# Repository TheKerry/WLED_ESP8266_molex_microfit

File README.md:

# WLED_ESP8266_molex_microfit

D1 will be assembled thr wrong way. It has to be rotated by 180° once the PCB arrives.

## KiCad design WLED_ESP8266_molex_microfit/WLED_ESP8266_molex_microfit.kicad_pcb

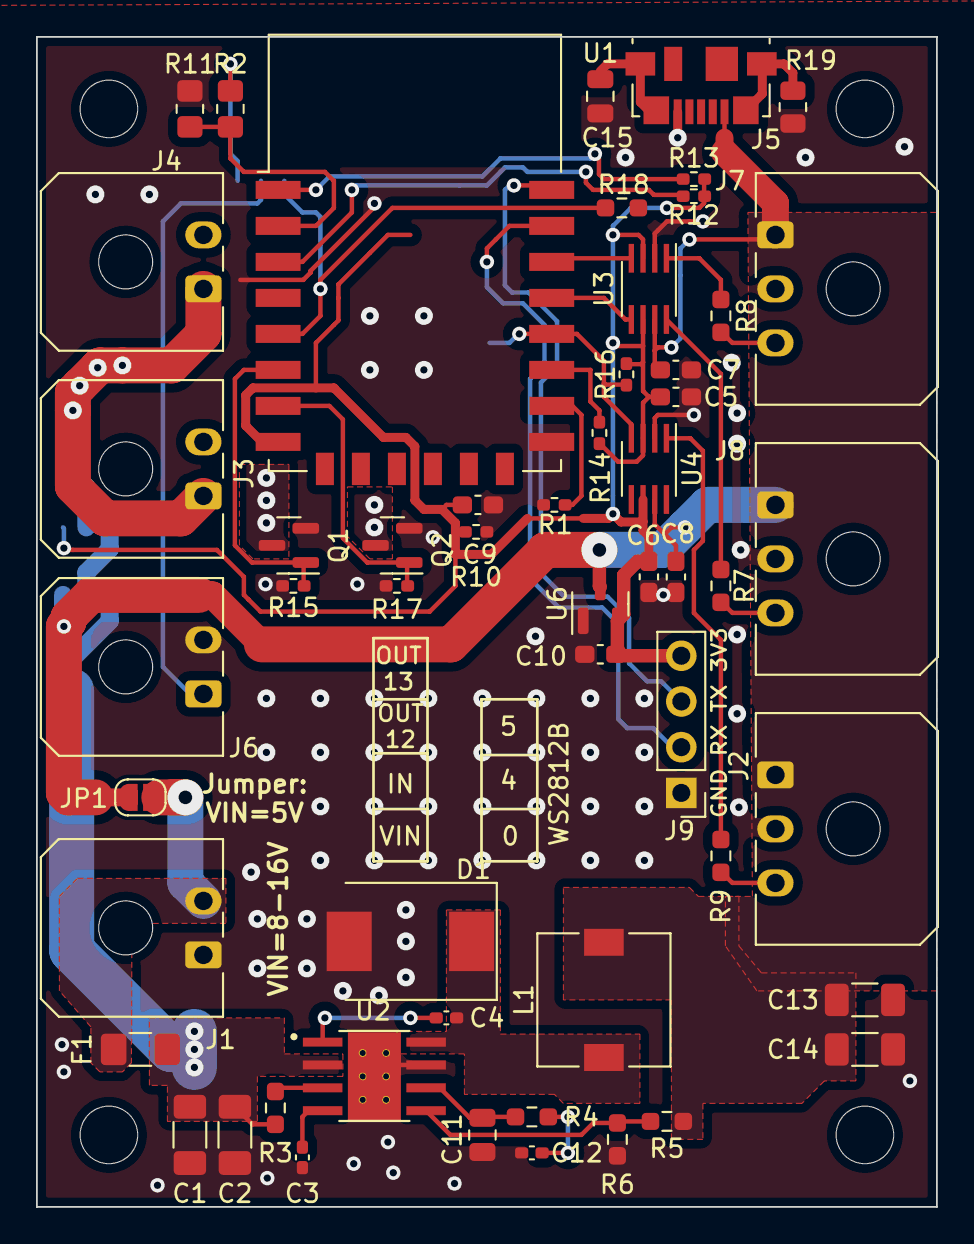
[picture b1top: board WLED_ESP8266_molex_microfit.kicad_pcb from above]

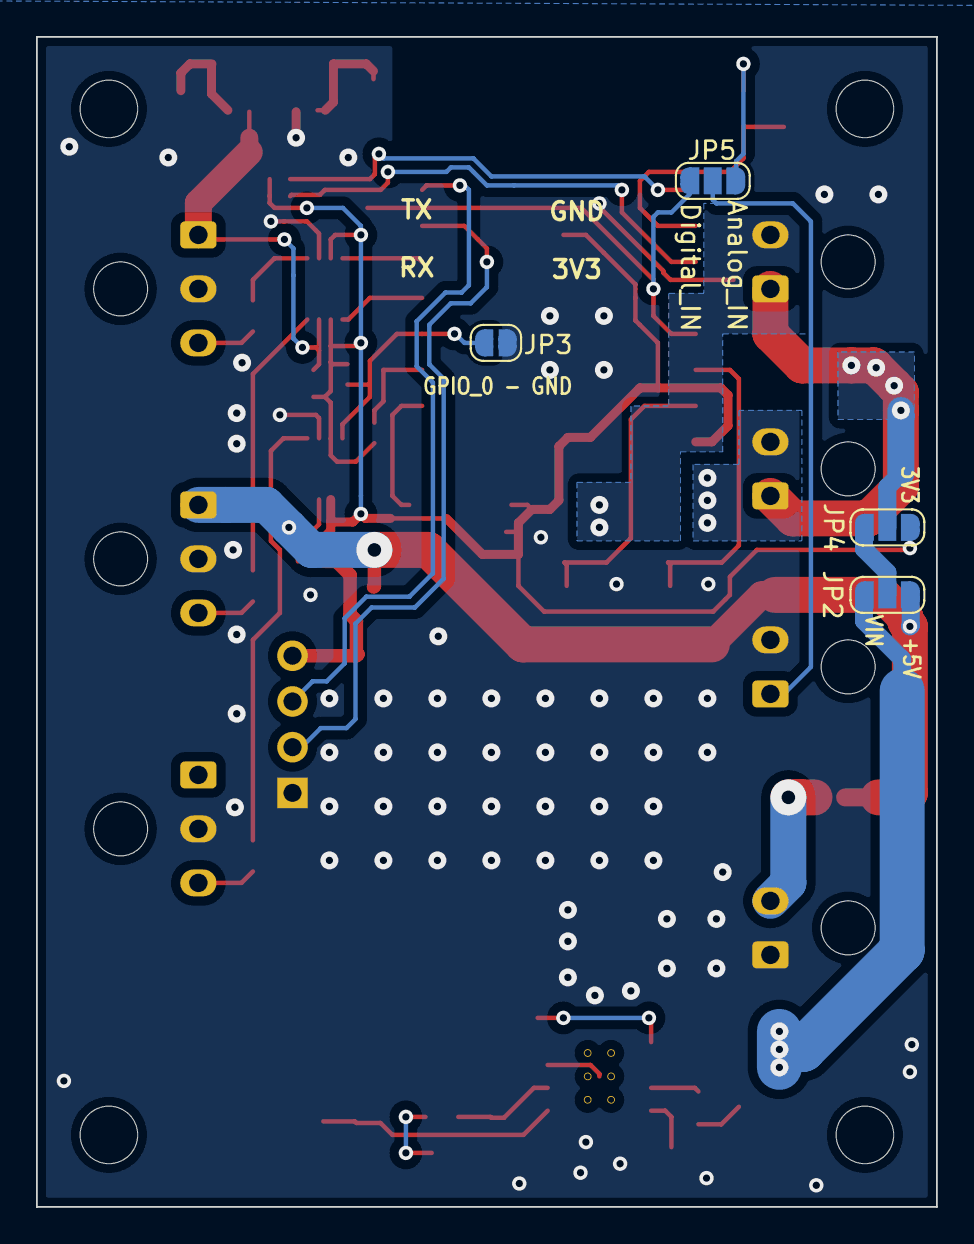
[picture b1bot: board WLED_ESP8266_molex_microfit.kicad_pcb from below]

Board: 2 copper layers, 50.0 x 65.0 mm, 62 parts (4 on the bottom side), 38 nets.

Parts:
C1, C2: 10uF; C_1206_3216Metric_Pad1.33x1.80mm_HandSolder
C3: 22uF; C_0402_1005Metric_Pad0.74x0.62mm_HandSolder
C4, C12: 100nF; C_0402_1005Metric_Pad0.74x0.62mm_HandSolder
C5, C6, C7, C8, C9, C10: 100nF; C_0603_1608Metric_Pad1.08x0.95mm_HandSolder
C11: 10pF; C_0805_2012Metric
C13, C14: 47uF; C_1206_3216Metric_Pad1.33x1.80mm_HandSolder
C15: 0.01uF; C_0805_2012Metric
D1: B340; D_SMC
F1: 5A; Fuse_1206_3216Metric_Pad1.42x1.75mm_HandSolder
H1, H2, H3, H4: MountingHole; MountingHole_3.2mm_M3_DIN965
J1, J3, J4, J6: Molex Micro-fit 2x1; Molex_Micro-Fit_3.0_43650-0200_1x02_P3.00mm_Horizontal
J2, J7, J8: Molex Micro-fit 3x1; Molex_Micro-Fit_3.0_43650-0300_1x03_P3.00mm_Horizontal
J5: USB_B_Micro; USB_Micro-B_Molex_47346-0001
J9: Conn_01x04_Male; PinHeader_1x04_P2.54mm_Vertical
JP1, JP3: SolderJumper_2_Open; SolderJumper-2_P1.3mm_Open_RoundedPad1.0x1.5mm
JP2, JP4, JP5: SolderJumper_3_Open; SolderJumper-3_P1.3mm_Open_RoundedPad1.0x1.5mm_NumberLabels
L1: 6.8uH; L_7.3x7.3_H3.5
Q1, Q2: AO3401A; SOT-23
R1, R10, R12, R13, R14, R15, R16, R17: 10k; R_0402_1005Metric_Pad0.72x0.64mm_HandSolder
R2: 68k; R_0805_2012Metric_Pad1.20x1.40mm_HandSolder
R3: 0; R_0603_1608Metric_Pad0.98x0.95mm_HandSolder
R4: 61.9k; R_0603_1608Metric_Pad0.98x0.95mm_HandSolder
R5: 10.2k; R_0603_1608Metric_Pad0.98x0.95mm_HandSolder
R6: 1.96k; R_0603_1608Metric_Pad0.98x0.95mm_HandSolder
R7, R8, R9: 300; R_0603_1608Metric_Pad0.98x0.95mm_HandSolder
R11: 4.7k; R_0805_2012Metric_Pad1.20x1.40mm_HandSolder
R18: 10k; R_0603_1608Metric_Pad0.98x0.95mm_HandSolder
R19: 1M; R_0805_2012Metric
U1: ESP-12F; ESP-12E
U2: TPS54331DDAR; CONV_TPS54331DDAR
U3, U4: TXS0102DCT; SSOP-8_2.95x2.8mm_P0.65mm
U6: ME6211A33M3G-N; SOT-23

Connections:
+3V3: C5.2, C6.2, C9.2, C10.2, J9.4, JP4.1 (A), R10.2, R12.2, R13.2, R14.2, R16.2, R18.2, U1.8 (VCC), U3.3 (VCCA), U3.6 (OE), U4.3 (VCCA), U4.6 (OE), U6.2 (VO)
+5V: C7.1, C8.1, C13.1, C14.1, J2.1, J5.1 (VBUS), J7.1, J8.1, JP1.2 (B), JP2.1 (A), L1.2, R5.2, U3.7 (VCCB), U4.7 (VCCB), U6.3 (VI)
/Q1_Drain: J3.2, Q1.3 (D)
/Q2_Drain: J4.2, Q2.3 (D)
/TPS_PH: C4.2, D1.1 (K), L1.1, U2.8 (PH)
ADC: JP5.1 (A), R2.1
EN: R12.1, U1.3 (EN)
GND: C1.2, C2.2, C3.1, C5.1, C6.1, C7.2, C8.2, C9.1, C10.1, C11.1, C12.1, C13.2, C14.2, C15.2, D1.2 (A), J1.1, J2.2, J5.5 (GND), J6.2, J7.2, J8.2, J9.1, JP3.2 (B), Q1.2 (S), Q2.2 (S), R1.1, R6.1, R10.1, R11.2, R15.1, R17.1, R19.2, U1.15 (GND), U2.7 (GND), U2.9 (POWERPAD), U3.2 (GND), U4.2 (GND), U6.1 (GND)
GND1: C15.1, J5.6 (Shield), R19.1
GPIO_0: JP3.1 (A), R16.1, U1.18 (GPIO0), U4.4 (A2)
GPIO_2: R14.1, U1.17 (GPIO2)
GPIO_4: U1.19 (GPIO4), U3.5 (A1)
GPIO_5: U1.20 (GPIO5), U3.4 (A2)
GPIO_12: Q1.1 (G), R15.2, U1.6 (GPIO12)
GPIO_13: Q2.1 (G), R17.2, U1.7 (GPIO13)
GPIO_14: JP5.3 (B), R18.1, U1.5 (GPIO14)
GPIO_15: R1.2, U1.16 (GPIO15)
MOSFET_VOLTAGE: J3.1, J4.1, JP4.2 (C)
unnamed: C3.2, U2.4 (SS)
unnamed: C4.1, U2.1 (BOOT)
unnamed: C11.2, R4.1, U2.6 (COMP)
unnamed: C12.2, R4.2
unnamed: J6.1, JP5.2 (C)
unnamed: JP2.2 (C), JP4.3 (B)
unnamed: R3.2, U2.3 (EN)
unnamed: R7.1, U3.8 (B1)
unnamed: R8.1, U3.1 (B2)
unnamed: R9.1, U4.1 (B2)
unnamed: R2.2, R11.1, U1.2 (ADC)
RST: R13.1, U1.1 (~RST)
RX: J9.2, U1.21 (GPIO3/RXD)
TPS_VSENSE: R5.1, R6.2, U2.5 (VSENSE)
TX: J9.3, U1.22 (GPIO1/TXD)
VIN: F1.1, J1.2, JP1.1 (A)
VIN_F: C1.1, C2.1, F1.2, JP2.3 (B), R3.1, U2.2 (VIN)
WS2812B_GPIO_0: J2.3, R9.2
WS2812B_GPIO_4: J8.3, R7.2
WS2812B_GPIO_5: J7.3, R8.2

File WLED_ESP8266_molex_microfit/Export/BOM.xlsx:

Comment | Designator | Footprint | LCSC
10uF | C1,C2 | Capacitor_SMD:C_1206_3216Metric_Pad1.33x1.80mm_HandSolder | C13585
10pF | C11 | Capacitor_SMD:C_0805_2012Metric | C1785
47uF | C13,C14 | Capacitor_SMD:C_1206_3216Metric_Pad1.33x1.80mm_HandSolder | C96123
0.01uF | C15 | Capacitor_SMD:C_0805_2012Metric | C1710
22uF | C3 | Capacitor_SMD:C_0402_1005Metric_Pad0.74x0.62mm_HandSolder
100nF | C4,C12 | Capacitor_SMD:C_0402_1005Metric_Pad0.74x0.62mm_HandSolder | C1525
100nF | C5,C6,C7,C8,C9,C10 | Capacitor_SMD:C_0603_1608Metric_Pad1.08x0.95mm_HandSolder | C14663
B340 | D1 | Diode_SMD:D_SMC | C64982
5A | F1 | Fuse:Fuse_1206_3216Metric_Pad1.42x1.75mm_HandSolder
MountingHole | H1,H2,H3,H4 | MountingHole:MountingHole_3.2mm_M3_DIN965
Molex Micro-fit 2x1 | J1,J3,J4,J6 | Connector_Molex:Molex_Micro-Fit_3.0_43650-0200_1x02_P3.00mm_Horizontal
Molex Micro-fit 3x1 | J2,J7,J8 | Connector_Molex:Molex_Micro-Fit_3.0_43650-0300_1x03_P3.00mm_Horizontal
USB_B_Micro | J5 | Connector_USB:USB_Micro-B_Molex_47346-0001
Conn_01x04_Male | J9 | Connector_PinHeader_2.54mm:PinHeader_1x04_P2.54mm_Vertical
SolderJumper_2_Open | JP1,JP3 | Jumper:SolderJumper-2_P1.3mm_Open_RoundedPad1.0x1.5mm
SolderJumper_3_Open | JP2,JP4,JP5 | Jumper:SolderJumper-3_P1.3mm_Open_RoundedPad1.0x1.5mm_NumberLabels
6.8uH | L1 | Inductor_SMD:L_10.4x10.4_H4.8 | C408449
AO3401A | Q1,Q2 | Package_TO_SOT_SMD:SOT-23 | C15127
10k | R1,R10,R12,R13,R14,R15,R16,R17 | Resistor_SMD:R_0402_1005Metric_Pad0.72x0.64mm_HandSolder | C25744
4.7k | R11 | Resistor_SMD:R_0805_2012Metric_Pad1.20x1.40mm_HandSolder | C23162
10k | R18 | Resistor_SMD:R_0603_1608Metric_Pad0.98x0.95mm_HandSolder | C25804
1M | R19 | Resistor_SMD:R_0805_2012Metric | C17514
68k | R2 | Resistor_SMD:R_0805_2012Metric_Pad1.20x1.40mm_HandSolder | C17801
0 | R3 | Resistor_SMD:R_0603_1608Metric_Pad0.98x0.95mm_HandSolder | C21189
61.9k | R4 | Resistor_SMD:R_0603_1608Metric_Pad0.98x0.95mm_HandSolder | C23221
10.2k | R5 | Resistor_SMD:R_0603_1608Metric_Pad0.98x0.95mm_HandSolder | C25804
1.96k | R6 | Resistor_SMD:R_0603_1608Metric_Pad0.98x0.95mm_HandSolder | C22975
300 | R7,R8,R9 | Resistor_SMD:R_0603_1608Metric_Pad0.98x0.95mm_HandSolder | C23025
ESP-12F | U1 | RF_Module:ESP-12E
TPS54331DDAR | U2 | CONV_TPS54331DDAR | C9865
TXS0102DCT | U3,U4 | Package_SO:SSOP-8_2.95x2.8mm_P0.65mm
ME6211A33M3G-N | U6 | Package_TO_SOT_SMD:SOT-23 | C168807

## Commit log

2022-01-18 initial upload
2022-01-18 schematics updated
2022-01-23 V1 completed
2022-01-25 USB added
2022-01-29 Issue 28.01.Yannik_part1
2022-01-31 feedback implemented
2022-02-05 V2 in production
